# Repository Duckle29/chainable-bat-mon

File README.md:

# chainable-bat-mon
A daisy chainable battery monitor

This is a battery monitor meant to monitor lead acid batteries. If the battery voltage goes below a configurable set point, 
set by the potentiometer, the LED will turn on, and the optocoupler will pull the output line on the TRS connectors low.

To use the signal, supply 5v and gnd on the tip and sleeve of a 3.5mm mini-jack cable, and solder the jumper on one of the PCBs. Then just chain them together.
If the battery voltage goes low on any of the batteries, the signal line will go low.

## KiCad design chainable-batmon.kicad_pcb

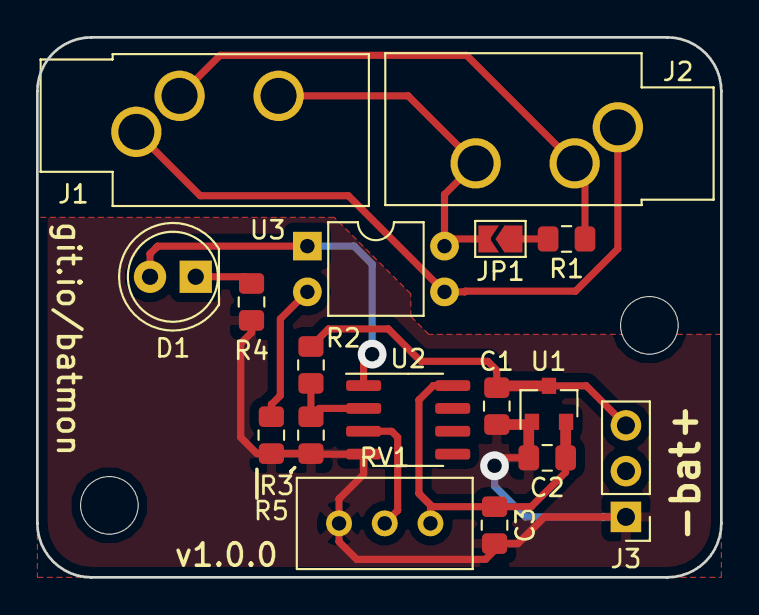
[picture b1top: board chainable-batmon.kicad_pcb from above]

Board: 2 copper layers, 38.0 x 30.0 mm, 17 parts (0 on the bottom side), 12 nets.

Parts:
C1: 1uF 25v; C_0805_2012Metric_Pad1.15x1.40mm_HandSolder
C2: 1uF 10v; C_0805_2012Metric_Pad1.15x1.40mm_HandSolder
C3: 100nF 10v; C_0805_2012Metric_Pad1.15x1.40mm_HandSolder
D1: LED; LED_D5.0mm
J1, J2: TRS-jack; Jack_3.5mm_CUI_SJ1-3533NG_Horizontal_CircularHoles
J3: Bat; PinHeader_1x03_P2.54mm_Vertical
JP1: jumper; SolderJumper-2_P1.3mm_Open_TrianglePad1.0x1.5mm
R1: 10k; R_0805_2012Metric_Pad1.15x1.40mm_HandSolder
R2: 470k; R_0805_2012Metric_Pad1.15x1.40mm_HandSolder
R3: 100k; R_0805_2012Metric_Pad1.15x1.40mm_HandSolder
R4: 1k; R_0805_2012Metric_Pad1.15x1.40mm_HandSolder
R5: 220R; R_0805_2012Metric_Pad1.15x1.40mm_HandSolder
RV1: 100k; Potentiometer_Bourns_3296W_Vertical
U1: MCP1700-5002E_SOT23; SOT-23
U2: LM393; SOIC-8_3.9x4.9mm_P1.27mm
U3: SFH617A-1; DIP-4_W7.62mm

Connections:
+5V: C2.1, C3.2, RV1.1, U1.2, U2.8
+BATT: C1.2, J3.3, R2.1, U1.3
-BATT: C1.1, C2.2, C3.1, J3.1, R3.2, R4.2, R5.2, RV1.3, U1.1, U2.4
/bat_low: J1.R, J2.R, JP1.2, U3.4
GND: J1.S, J2.S, U3.3
unnamed: D1.1, R4.1
unnamed: D1.2, U2.1, U3.1
unnamed: JP1.1, R1.2
unnamed: R2.2, R3.1, U2.2
unnamed: R5.1, U3.2
unnamed: RV1.2, U2.3
VCC: J1.T, J2.T, R1.1

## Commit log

2019-06-18 Added renders and updated readme
2019-06-18 Added schematic pdf
